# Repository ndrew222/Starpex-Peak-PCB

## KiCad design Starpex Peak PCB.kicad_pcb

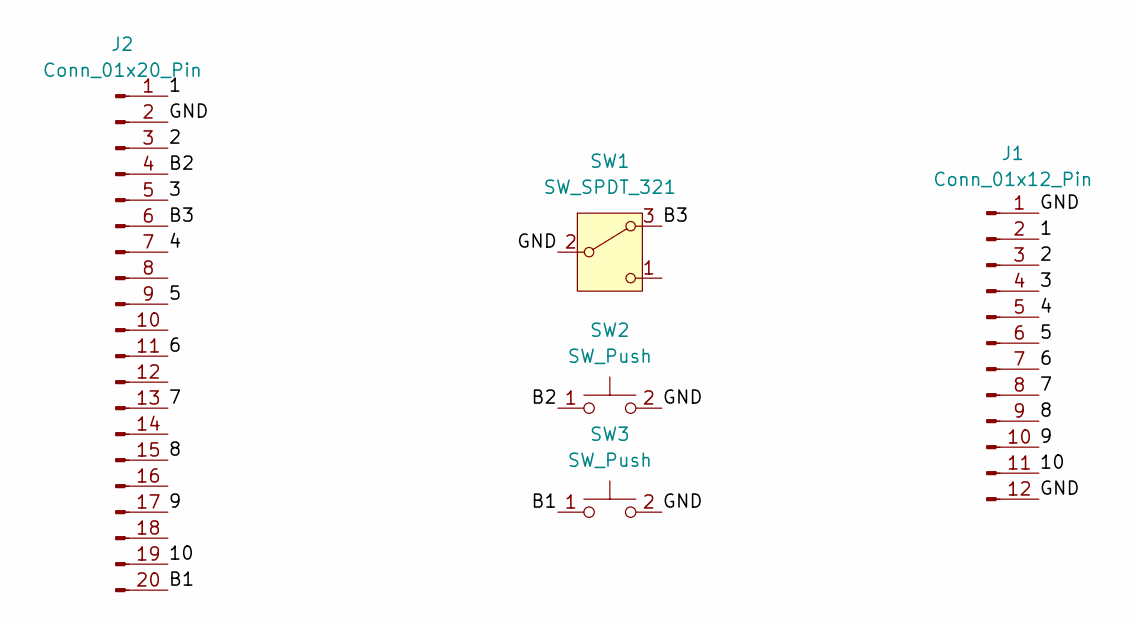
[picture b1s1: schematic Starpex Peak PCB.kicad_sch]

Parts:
J1: Conn_01x12_Pin; GH
J2: Conn_01x20_Pin; PinHeader_2x10_P2.54mm_Vertical
SW1: SW_SPDT_321; KW11
SW2, SW3: SW_Push; SW_Alps_Matias

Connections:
/1: J1.2, J2.1
/2: J1.3, J2.3
/3: J1.4, J2.5
/4: J1.5, J2.7
/5: J1.6, J2.9
/6: J1.7, J2.11
/7: J1.8, J2.13
/8: J1.9, J2.15
/9: J1.10, J2.17
/10: J1.11, J2.19
/B1: J2.20, SW3.1
/B2: J2.4, SW2.1
/B3: J2.6, SW1.3 (A)
/GND: J1.1, J1.12, J2.2, SW1.2 (B), SW2.2, SW3.2

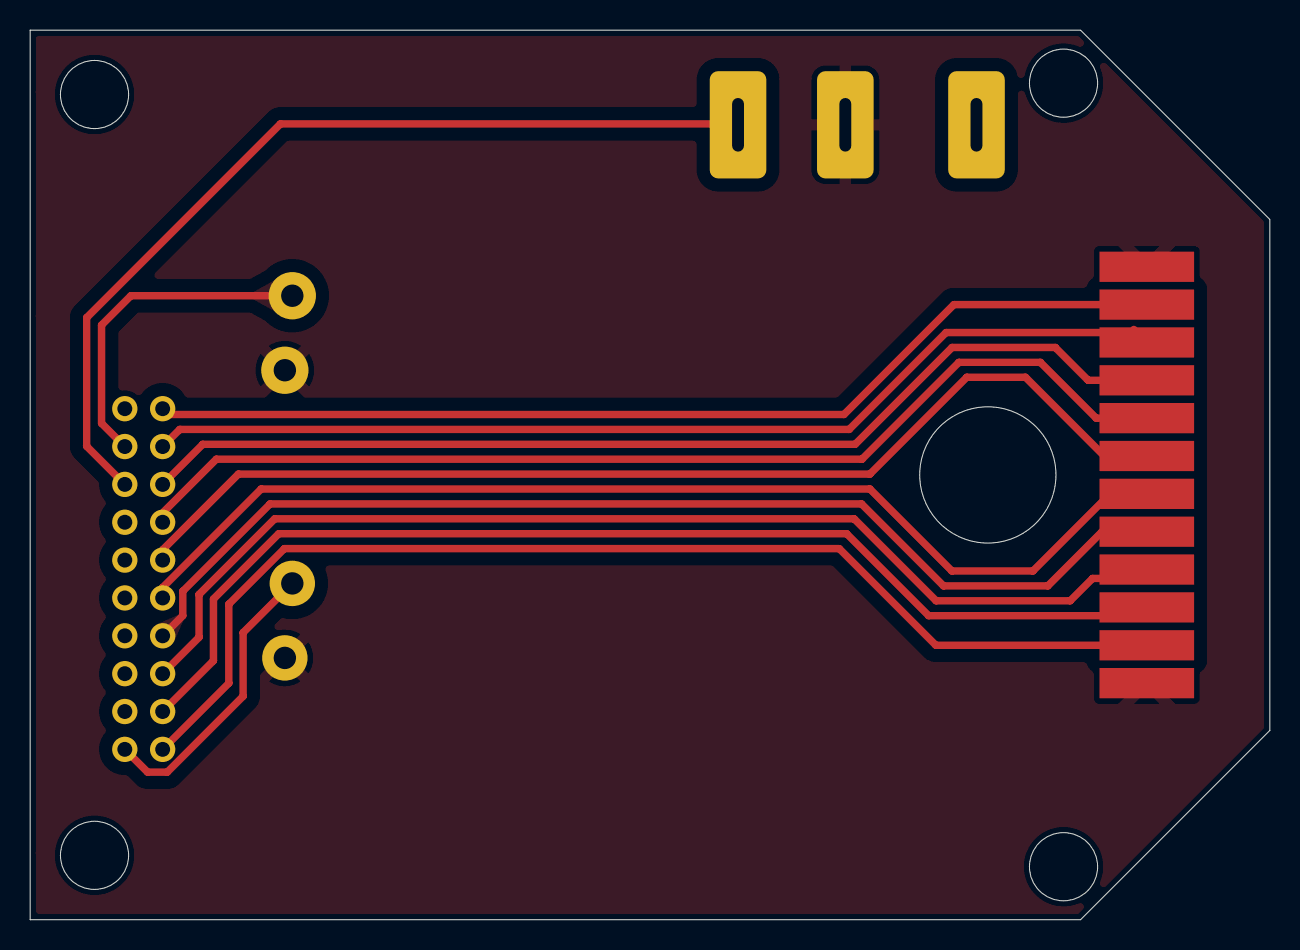
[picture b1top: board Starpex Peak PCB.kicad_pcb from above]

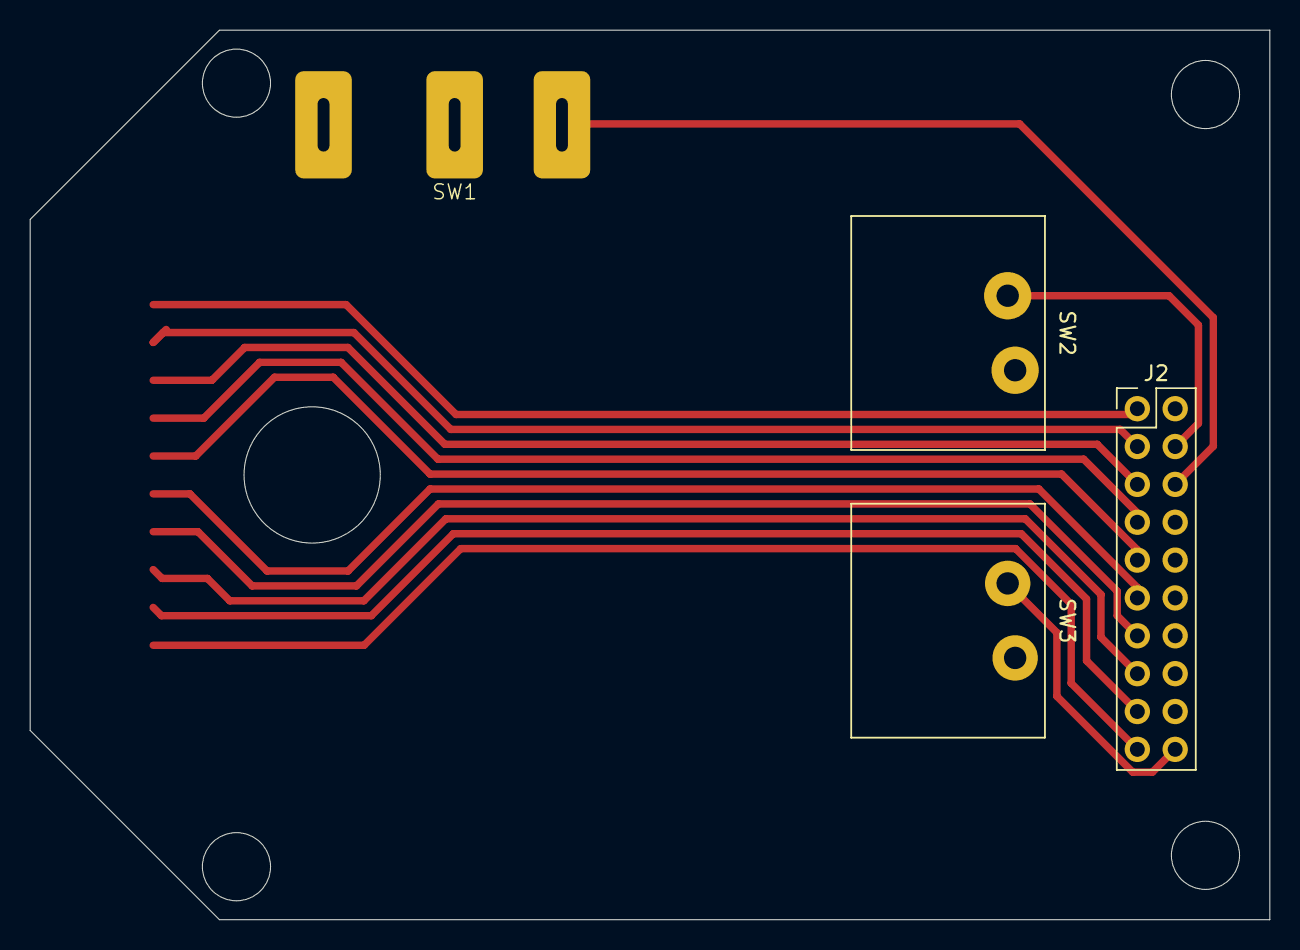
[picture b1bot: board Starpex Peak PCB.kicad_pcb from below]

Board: 2 copper layers, 83.2 x 59.7 mm, 5 parts (4 on the bottom side), 14 nets.

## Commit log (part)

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2025-10-23 Initial commit
    First test fabrication to test fit.
2025-11-03 1st Pink test print
2025-12-12 Peak PCB 1.0
    All traces ready. Now need to make daughterboard for RPi Pico
2025-12-24 Add CERN Open Hardware Licence
    Added CERN Open Hardware Licence Version 2 - Weakly Reciprocal to the project.
2026-04-14 update to latest version of KiCad
